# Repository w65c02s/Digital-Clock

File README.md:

## Digital Clock

### Introduction 
This is a clock is based on 74xx series TTL logic ICs. The clock pulse is generated by a 32.768kHz crystal which is further divided by divider ICs and a 1Hz pulse is obtained. This pulse is used to drive the seconds, minutes and hour counters. The display is a simple 7 segment LED display driven by 7447 BCD to 7 segment decoder.

The schematics and PCB has been designed in KiCad. This repository contains the complete KiCad project files made in version 6.0 of KiCad.

Refer the documenatation for complete details

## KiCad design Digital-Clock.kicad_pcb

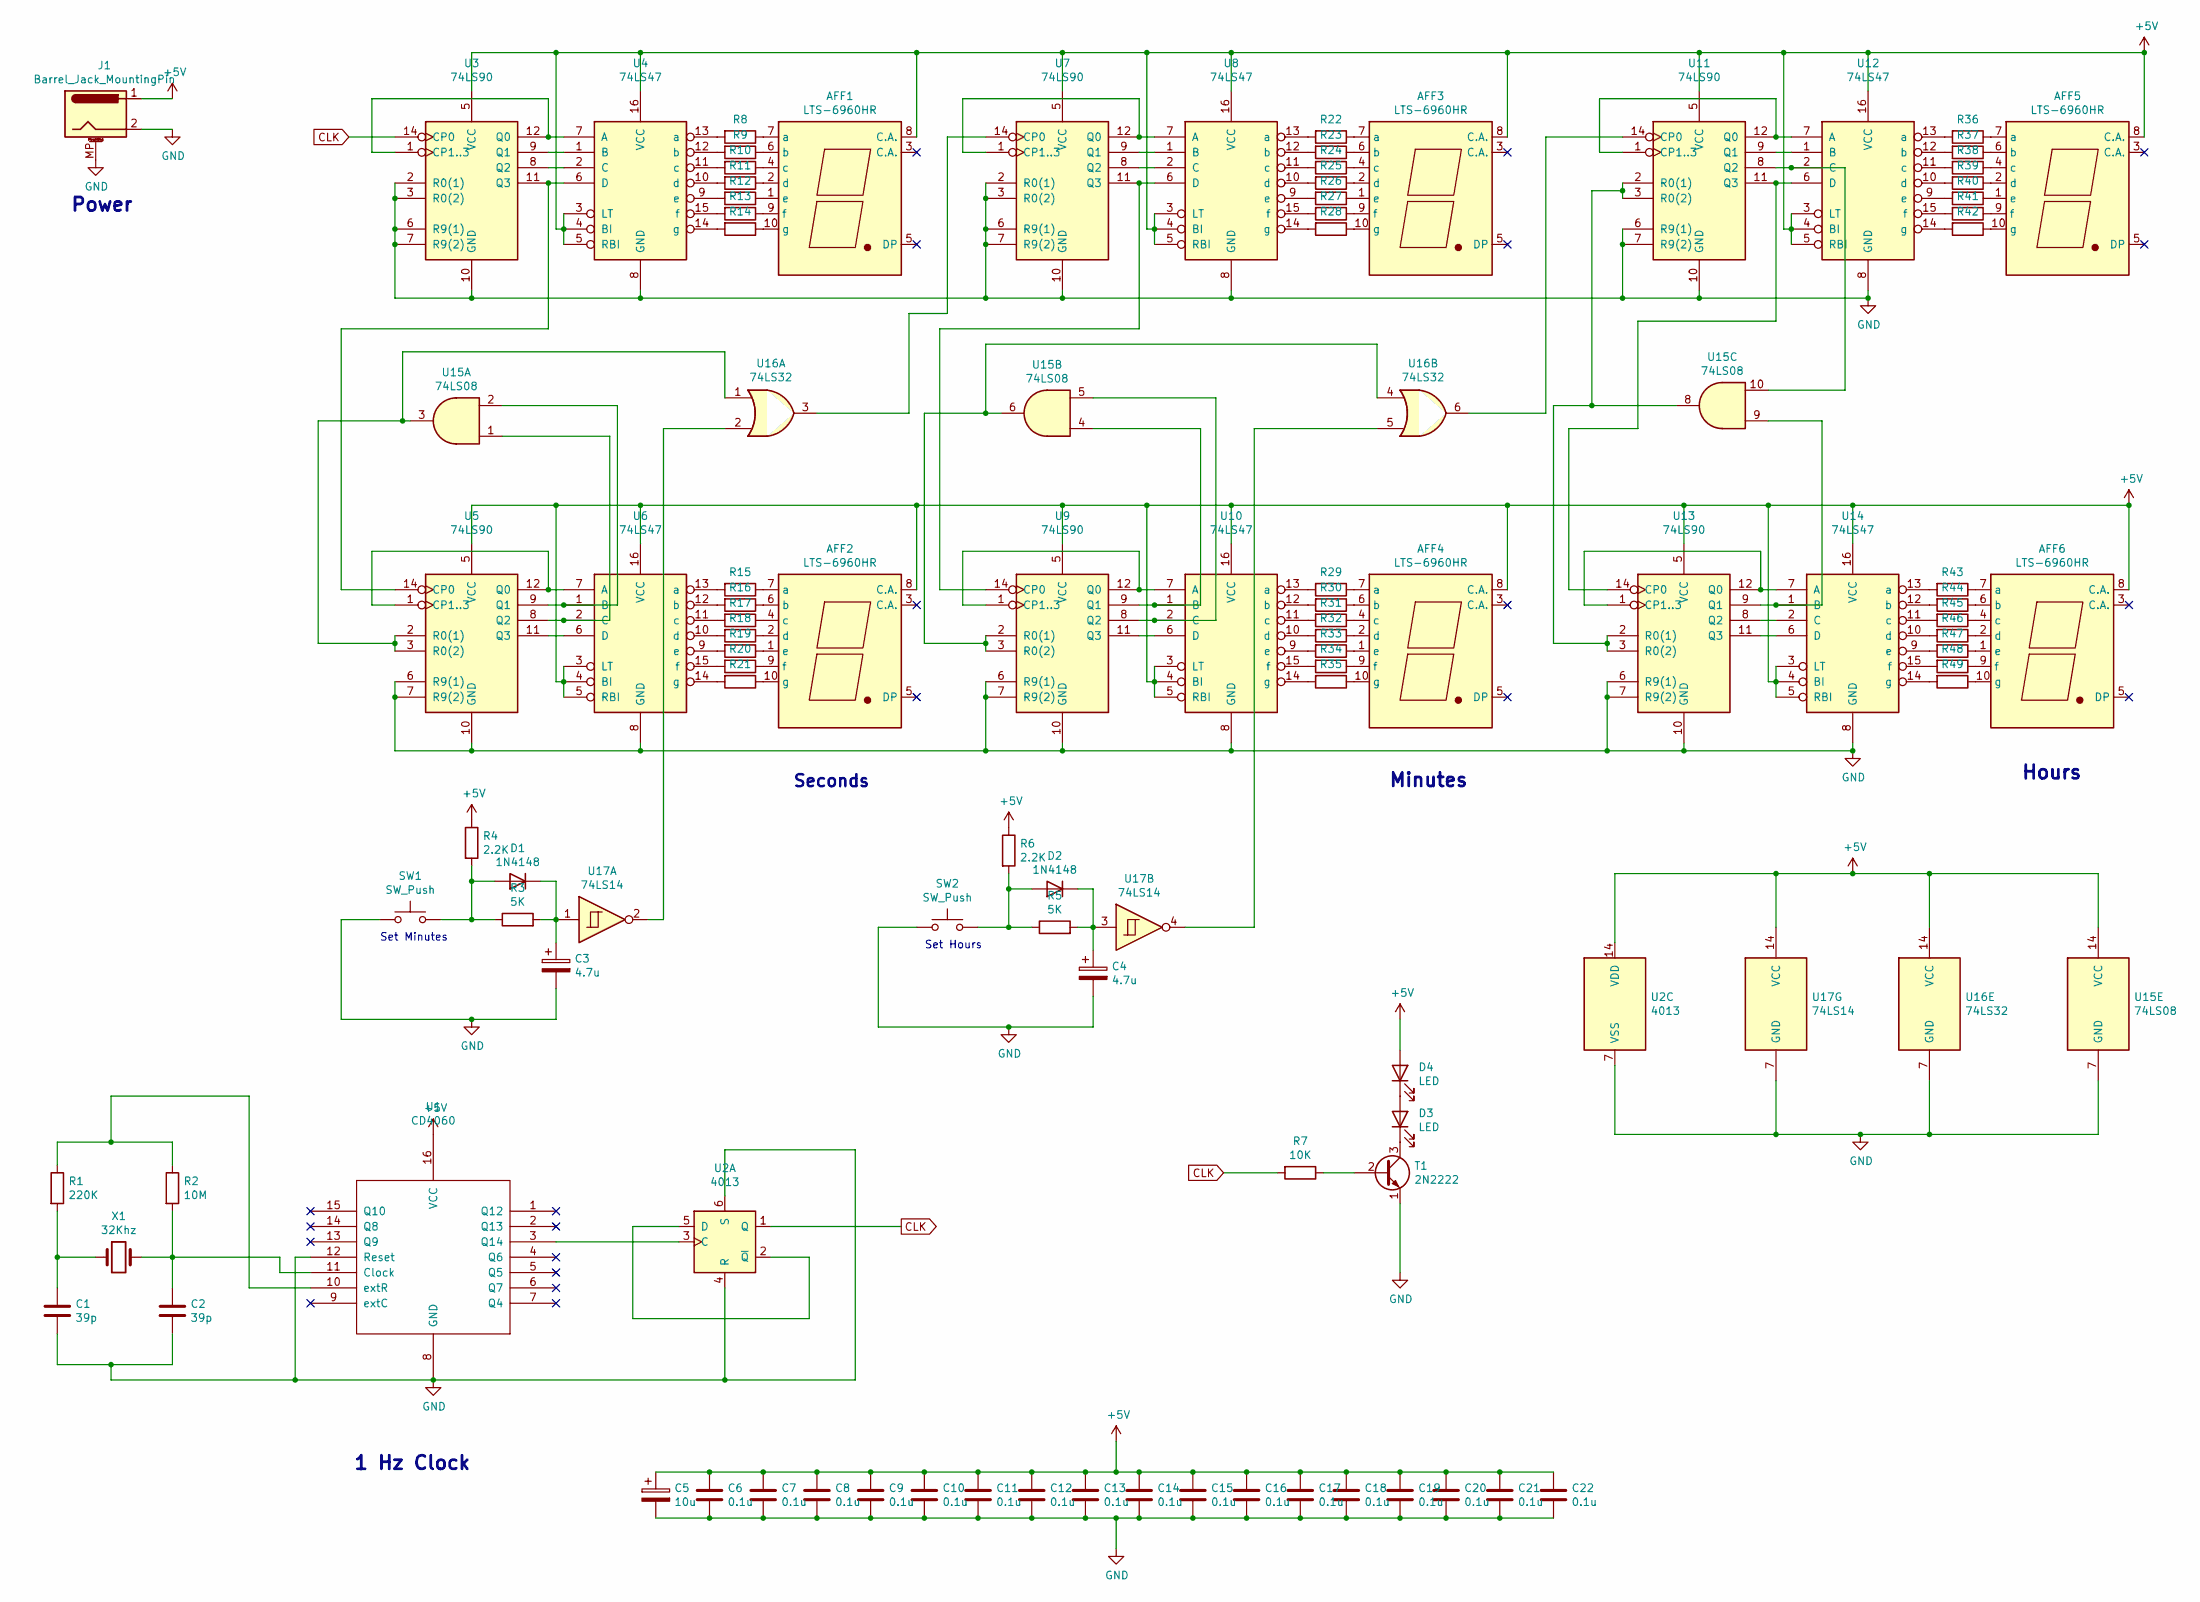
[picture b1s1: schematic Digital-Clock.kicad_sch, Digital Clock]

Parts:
AFF1, AFF2, AFF3, AFF4, AFF5, AFF6: LTS-6960HR; 7SegmentLED_LTS6760_LTS6780
C1, C2: 39p; C_Disc_D5.0mm_W2.5mm_P2.50mm
C3, C4: 4.7u; CP_Radial_D5.0mm_P2.50mm
C5: 10u; CP_Radial_D5.0mm_P2.50mm
C6, C7, C8, C9, C10, C11, C12, C13, C14, C15, C16, C17, C18, C19, C20, C21, C22: 0.1u; C_Disc_D5.0mm_W2.5mm_P2.50mm
D1, D2: 1N4148; D_DO-35_SOD27_P7.62mm_Horizontal
D3, D4: LED; LED_D3.0mm
J1: Barrel_Jack_MountingPin; BarrelJack_CUI_PJ-063AH_Horizontal
R1: 220K; R_Axial_DIN0207_L6.3mm_D2.5mm_P10.16mm_Horizontal
R2: 10M; R_Axial_DIN0207_L6.3mm_D2.5mm_P10.16mm_Horizontal
R3, R5: 5K; R_Axial_DIN0207_L6.3mm_D2.5mm_P10.16mm_Horizontal
R4, R6: 2.2K; R_Axial_DIN0207_L6.3mm_D2.5mm_P10.16mm_Horizontal
R7: 10K; R_Axial_DIN0207_L6.3mm_D2.5mm_P10.16mm_Horizontal
R8, R9, R10, R11, R12, R13, R14, R15, R16, R17, R18, R19, R20, R21, R22, R23, R24, R25, R26, R27, R28, R29, R30, R31, R32, R33, R34, R35, R36, R37, R38, R39, R40, R41, R42, R43, R44, R45, R46, R47, R48, R49: 220; R_Axial_DIN0207_L6.3mm_D2.5mm_P10.16mm_Horizontal
SW1, SW2: SW_Push; SW_PUSH_6mm
T1: 2N2222; TO-92
U1: CD4060; DIP-16_W7.62mm
U2: 4013; DIP-14_W7.62mm
U3, U5, U7, U9, U11, U13: 74LS90; DIP-14_W7.62mm
U4, U6, U8, U10, U12, U14: 74LS47; DIP-16_W7.62mm
U15: 74LS08; DIP-14_W7.62mm
U16: 74LS32; DIP-14_W7.62mm
U17: 74LS14; DIP-14_W7.62mm
X1: 32Khz; Crystal_Round_D1.0mm_Vertical

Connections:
+5V: AFF1.8 (C.A.), AFF2.8 (C.A.), AFF3.8 (C.A.), AFF4.8 (C.A.), AFF5.8 (C.A.), AFF6.8 (C.A.), C5.1, C6.1, C7.1, C8.1, C9.1, C10.1, C11.1, C12.1, C13.1, C14.1, C15.1, C16.1, C17.1, C18.1, C19.1, C20.1, C21.1, C22.1, D4.2 (A), J1.1, R4.1, R6.1, U1.16 (VCC), U2.14 (VDD), U3.5 (VCC), U4.3 (LT), U4.4 (BI), U4.5 (RBI), U4.16 (VCC), U5.5 (VCC), U6.3 (LT), U6.4 (BI), U6.5 (RBI), U6.16 (VCC), U7.5 (VCC), U8.3 (LT), U8.4 (BI), U8.5 (RBI), U8.16 (VCC), U9.5 (VCC), U10.3 (LT), U10.4 (BI), U10.5 (RBI), U10.16 (VCC), U11.5 (VCC), U12.3 (LT), U12.4 (BI), U12.5 (RBI), U12.16 (VCC), U13.5 (VCC), U14.3 (LT), U14.4 (BI), U14.5 (RBI), U14.16 (VCC), U15.14 (VCC), U16.14 (VCC), U17.14 (VCC)
CLK: R7.2, U2.1 (Q), U3.14 (CP0)
GND: C1.2, C2.2, C3.2, C4.2, C5.2, C6.2, C7.2, C8.2, C9.2, C10.2, C11.2, C12.2, C13.2, C14.2, C15.2, C16.2, C17.2, C18.2, C19.2, C20.2, C21.2, C22.2, J1.2, J1.MP (MountPin), SW1.1, SW2.1, T1.1 (E), U1.8 (GND), U1.12 (Reset), U2.4 (R), U2.6 (S), U2.7 (VSS), U3.2 (R0(1)), U3.3 (R0(2)), U3.6 (R9(1)), U3.7 (R9(2)), U3.10 (GND), U4.8 (GND), U5.6 (R9(1)), U5.7 (R9(2)), U5.10 (GND), U6.8 (GND), U7.2 (R0(1)), U7.3 (R0(2)), U7.6 (R9(1)), U7.7 (R9(2)), U7.10 (GND), U8.8 (GND), U9.6 (R9(1)), U9.7 (R9(2)), U9.10 (GND), U10.8 (GND), U11.6 (R9(1)), U11.7 (R9(2)), U11.10 (GND), U12.8 (GND), U13.6 (R9(1)), U13.7 (R9(2)), U13.10 (GND), U14.8 (GND), U15.7 (GND), U16.7 (GND), U17.7 (GND)
unnamed: AFF1.1 (e), R12.1
unnamed: AFF1.2 (d), R11.1
unnamed: AFF1.4 (c), R10.1
unnamed: AFF1.6 (b), R9.1
unnamed: AFF1.7 (a), R8.1
unnamed: AFF1.9 (f), R13.1
unnamed: AFF1.10 (g), R14.1
unnamed: AFF2.1 (e), R19.1
unnamed: AFF2.2 (d), R18.1
unnamed: AFF2.4 (c), R17.1
unnamed: AFF2.6 (b), R16.1
unnamed: AFF2.7 (a), R15.1
unnamed: AFF2.9 (f), R20.1
unnamed: AFF2.10 (g), R21.1
unnamed: AFF3.1 (e), R26.1
unnamed: AFF3.2 (d), R25.1
unnamed: AFF3.4 (c), R24.1
unnamed: AFF3.6 (b), R23.1
unnamed: AFF3.7 (a), R22.1
unnamed: AFF3.9 (f), R27.1
unnamed: AFF3.10 (g), R28.1
unnamed: AFF4.1 (e), R33.1
unnamed: AFF4.2 (d), R32.1
unnamed: AFF4.4 (c), R31.1
unnamed: AFF4.6 (b), R30.1
unnamed: AFF4.7 (a), R29.1
unnamed: AFF4.9 (f), R34.1
unnamed: AFF4.10 (g), R35.1
unnamed: AFF5.1 (e), R40.1
unnamed: AFF5.2 (d), R39.1
unnamed: AFF5.4 (c), R38.1
unnamed: AFF5.6 (b), R37.1
unnamed: AFF5.7 (a), R36.1
unnamed: AFF5.9 (f), R41.1
unnamed: AFF5.10 (g), R42.1
unnamed: AFF6.1 (e), R47.1
unnamed: AFF6.2 (d), R46.1
unnamed: AFF6.4 (c), R45.1
unnamed: AFF6.6 (b), R44.1
unnamed: AFF6.7 (a), R43.1
unnamed: AFF6.9 (f), R48.1
unnamed: AFF6.10 (g), R49.1
unnamed: C1.1, R1.2, X1.1
unnamed: C2.1, R2.2, U1.11 (Clock), X1.2
unnamed: C3.1, D1.1 (K), R3.2, U17.1
unnamed: C4.1, D2.1 (K), R5.2, U17.3
unnamed: D1.2 (A), R3.1, R4.2, SW1.2
unnamed: D2.2 (A), R5.1, R6.2, SW2.2
unnamed: D3.1 (K), T1.3 (C)
unnamed: D3.2 (A), D4.1 (K)
unnamed: R1.1, R2.1, U1.10 (extR)
unnamed: R7.1, T1.2 (B)
unnamed: R8.2, U4.13 (a)
unnamed: R9.2, U4.12 (b)
unnamed: R10.2, U4.11 (c)
unnamed: R11.2, U4.10 (d)
unnamed: R12.2, U4.9 (e)
unnamed: R13.2, U4.15 (f)
unnamed: R14.2, U4.14 (g)
unnamed: R15.2, U6.13 (a)
unnamed: R16.2, U6.12 (b)
unnamed: R17.2, U6.11 (c)
unnamed: R18.2, U6.10 (d)
unnamed: R19.2, U6.9 (e)
unnamed: R20.2, U6.15 (f)
unnamed: R21.2, U6.14 (g)
unnamed: R22.2, U8.13 (a)
unnamed: R23.2, U8.12 (b)
unnamed: R24.2, U8.11 (c)
unnamed: R25.2, U8.10 (d)
unnamed: R26.2, U8.9 (e)
unnamed: R27.2, U8.15 (f)
unnamed: R28.2, U8.14 (g)
unnamed: R29.2, U10.13 (a)
unnamed: R30.2, U10.12 (b)
unnamed: R31.2, U10.11 (c)
unnamed: R32.2, U10.10 (d)
unnamed: R33.2, U10.9 (e)
unnamed: R34.2, U10.15 (f)
unnamed: R35.2, U10.14 (g)
unnamed: R36.2, U12.13 (a)
unnamed: R37.2, U12.12 (b)
unnamed: R38.2, U12.11 (c)
unnamed: R39.2, U12.10 (d)
unnamed: R40.2, U12.9 (e)
unnamed: R41.2, U12.15 (f)
unnamed: R42.2, U12.14 (g)
unnamed: R43.2, U14.13 (a)
unnamed: R44.2, U14.12 (b)
unnamed: R45.2, U14.11 (c)
unnamed: R46.2, U14.10 (d)
unnamed: R47.2, U14.9 (e)
unnamed: R48.2, U14.15 (f)
unnamed: R49.2, U14.14 (g)
unnamed: U1.3 (Q14), U2.3 (C)
unnamed: U2.2 (~Q), U2.5 (D)
unnamed: U3.1 (CP1..3), U3.12 (Q0), U4.7 (A)
unnamed: U3.8 (Q2), U4.2 (C)
unnamed: U3.9 (Q1), U4.1 (B)
unnamed: U3.11 (Q3), U4.6 (D), U5.14 (CP0)
unnamed: U5.1 (CP1..3), U5.12 (Q0), U6.7 (A)
unnamed: U5.11 (Q3), U6.6 (D)
unnamed: U7.1 (CP1..3), U7.12 (Q0), U8.7 (A)
unnamed: U7.8 (Q2), U8.2 (C)
unnamed: U7.9 (Q1), U8.1 (B)
unnamed: U7.11 (Q3), U8.6 (D), U9.14 (CP0)
unnamed: U9.9 (Q1), U10.1 (B), U15.4
unnamed: U9.8 (Q2), U10.2 (C), U15.5
unnamed: U9.11 (Q3), U10.6 (D)
unnamed: U9.1 (CP1..3), U9.12 (Q0), U10.7 (A)
unnamed: U11.1 (CP1..3), U11.12 (Q0), U12.7 (A)
unnamed: U11.2 (R0(1)), U11.3 (R0(2)), U13.2 (R0(1)), U13.3 (R0(2)), U15.8
unnamed: U11.8 (Q2), U12.2 (C), U15.10
unnamed: U11.9 (Q1), U12.1 (B)
unnamed: U11.11 (Q3), U12.6 (D), U13.14 (CP0)
unnamed: U11.14 (CP0), U16.6
unnamed: U13.1 (CP1..3), U13.12 (Q0), U14.7 (A)
unnamed: U13.8 (Q2), U14.2 (C)
unnamed: U13.9 (Q1), U14.1 (B), U15.9
unnamed: U13.11 (Q3), U14.6 (D)
unnamed: U5.8 (Q2), U6.2 (C), U15.1
unnamed: U5.9 (Q1), U6.1 (B), U15.2
unnamed: U5.2 (R0(1)), U5.3 (R0(2)), U15.3, U16.1
unnamed: U9.2 (R0(1)), U9.3 (R0(2)), U15.6, U16.4
unnamed: U16.2, U17.2
unnamed: U7.14 (CP0), U16.3
unnamed: U16.5, U17.4

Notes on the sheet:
Minutes
Set Hours
Seconds
Hours
1 Hz Clock
Set Minutes
Power

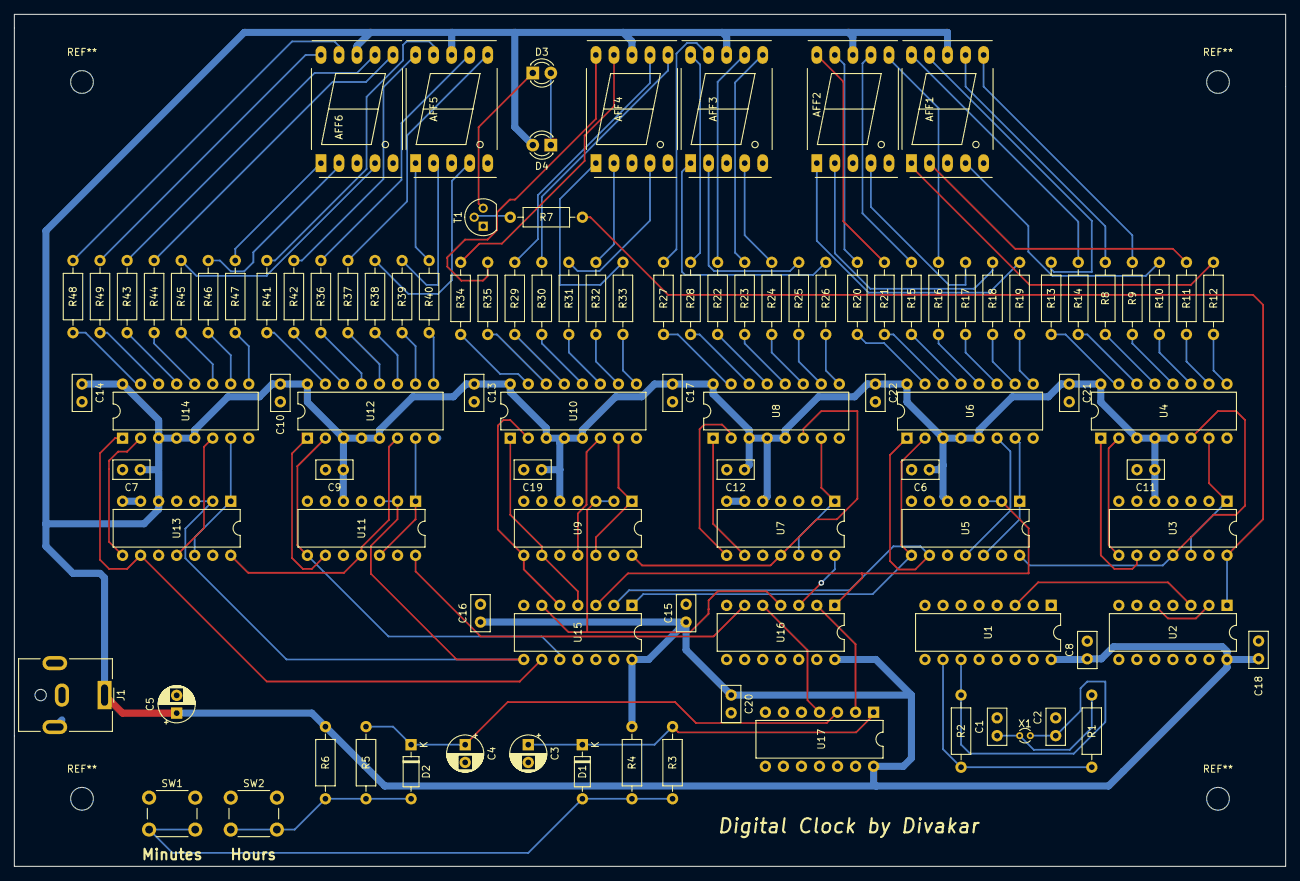
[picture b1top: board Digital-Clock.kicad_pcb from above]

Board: 2 copper layers, 179.1 x 120.0 mm, 103 parts (0 on the bottom side), 130 nets.

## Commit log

2022-11-06 First draft of documentation
2022-12-04 Add files via upload
    Updated
2024-08-08 updated files for Kicad 6.0
2024-08-13 Datasheets added
